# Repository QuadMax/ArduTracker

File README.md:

# ArduTracker

The ArduTracker is a light weight, easy to build FPV Tracker. It uses the downlink of the audio channel from the Transmitter as telemetry link. But this project is different from most others. ArduTracker is a continuous 360° degree Tracker with a special hinge. This [Video](https://vimeo.com/3991479) shows it best.

***

##[Wiki](https://github.com/QuadMax/ArduTracker/wiki) --||-- [RoadMap](https://github.com/QuadMax/ArduTracker/wiki/RoadMap)
***

###Milestone [0.9.0]
Today the compass could be implemented. This take us a step closer to a stable Version that has got all features.
The system´s components could be tested succesfully each by their own.
A whole system test comes soon.
* **This is new:**
 * implemented compass

###Milestone [0.8.1]
We are close leaving BETA! Heureka.
* **This is new:**
* The pcb design have been reworked. Now we got a groundstation that could power up 5 more devices. With 35um copper thickness it could bear 3 Ampere or 4.5 Ampere with 70um copper thickness.
* Furthermore the code got a rework too.
  * implemented cesco1´s PSK modem instead FSK
  * implemented 270 degree servos
  * implemented display / Menu / buttons
  * implemented servo invert with jumper on the uno shield

### Milestone [0.1.1]
* New pcb design with power distribution. 
  Now you could power up 3 more devices of your ground station with the pcb. Up to 2.5 Ampere. with 35um copper thickness.

### Milestone [0.1.0]
* pcb design first try

### Milestone [0.0.1]
* released Alpha

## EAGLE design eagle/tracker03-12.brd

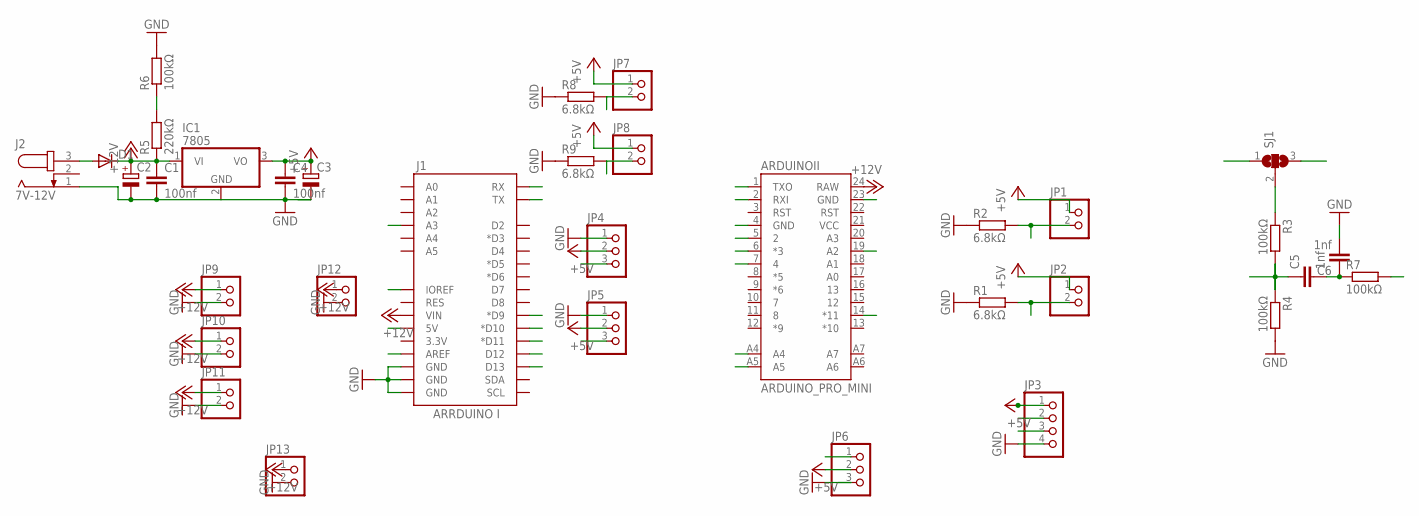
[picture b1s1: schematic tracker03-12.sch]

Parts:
ARDUINOII: ARDUINO_PRO_MINI
C1, C4: 100nf; C050-025X075
C2: CPOL-EUE3.5-8; E3,5-8
C3: CPOL-EUE2.5-5; E2,5-5
C5, C6: 1nf; C050-025X075
D1: 1N4004; DO41-10
IC1: 7805; TO220V
J1: ARRDUINO I; UNO_R3_SHIELD_NOLABELS
J2: 7V-12V; SPC4077
JP1, JP2, JP7, JP8, JP9, JP10, JP11, JP12, JP13: PINHD-1X2; 1X02
JP3: PINHD-1X4; 1X04
JP4, JP5, JP6: PINHD-1X3; 1X03
R1, R2, R8, R9: 6.8kΩ; 0204V
R3, R4, R6, R7: 100kΩ; 0204V
R5: 220kΩ; 0204V
SJ1: SJ2W; SJ_2

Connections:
5VA: J1.5V, SJ1.3
+5V: C3.+, C4.1, IC1.3 (VO), JP1.1, JP2.1, JP3.1, JP4.2, JP5.2, JP6.2, JP7.1, JP8.1
+12V: ARDUINOII.24 (RAW), C1.1, C2.+, D1.C, IC1.1 (VI), J1.VIN, JP9.1, JP10.1, JP11.1, JP12.1, JP13.1, R5.1
A2: ARDUINOII.19 (A2), R5.2, R6.1
A3: C5.1, J1.A3, R3.2, R4.1
A4: ARDUINOII.A4, JP3.2
A5: ARDUINOII.A5, JP3.3
AREF: J1.AREF, SJ1.1
AUDIO: R7.2
D2: ARDUINOII.5 (2), JP1.2, R2.2
D3: ARDUINOII.6 (*3)
D4: ARDUINOII.7 (4), JP2.2, R1.2
D9: J1.D9 (*D9), JP4.3
D10: J1.D10 (*D10), JP5.3
D11: ARDUINOII.14 (*11), JP6.1
D11A1: J1.D11 (*D11), JP7.2, R8.2
D12: J1.D12, JP8.2, R9.2
D13: J1.D13
GND: ARDUINOII.4 (GND), ARDUINOII.23 (GND), C1.2, C2.-, C3.-, C4.2, C6.2, IC1.2 (GND), J1.GND@0 (GND), J1.GND@1 (GND), J1.GND@2 (GND), J2.1, JP3.4, JP4.1, JP5.1, JP6.3, JP9.2, JP10.2, JP11.2, JP12.2, JP13.2, R1.1, R2.1, R4.2, R6.2, R8.1, R9.1
unnamed: D1.A, J2.3
unnamed: R3.1, SJ1.2
unnamed: C5.2, C6.1, R7.1
RX: ARDUINOII.1 (TXO), J1.RX
TX: ARDUINOII.2 (RXI), J1.TX

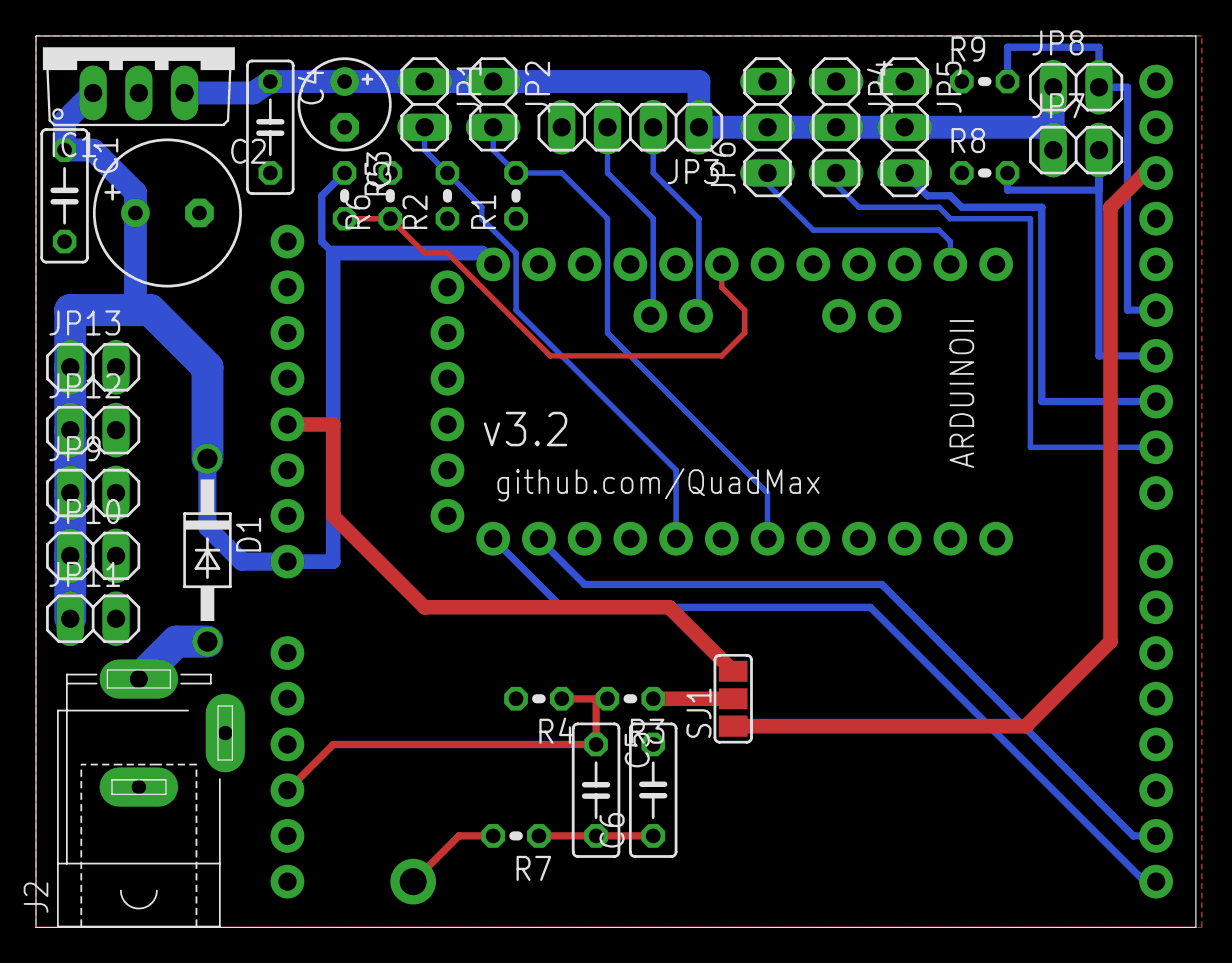
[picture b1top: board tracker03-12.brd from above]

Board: 2 copper layers, 64.4 x 49.5 mm, 34 parts (0 on the bottom side), 21 nets.

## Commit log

2015-06-29 :octocat: Added .gitattributes & .gitignore files
2015-06-29 test
2015-06-29 Version [0.0.1]
2015-06-29 Version[0.0.1]
2015-06-30 Version [0.1.0]
2015-07-18 Preparing next big milestone
2015-07-19 from Cesco1
2015-07-19 asdf
2015-07-19 bug fix
2015-07-23 first dry
2015-07-23 Revert "first dry"
    This reverts commit 7e4aa39fc547326ef01375a12e2c486fc155cf8f.
2015-07-23 Revert "Revert "first dry""
    This reverts commit c0850195adbc13ca56c05269b1c6c324b066d972.
2015-07-23 first try
2015-07-23 major update
2015-07-26 implemented PSK
2015-07-26 1.1.0
2015-07-27 0.2.0
2015-07-31 Create gh-pages branch via GitHub

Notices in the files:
parts and their libraries:
SparkFun-Boards: Licensing: Creative Commons ShareAlike 4.0 International - https://creativecommons.org/licenses/by-sa/4.0
